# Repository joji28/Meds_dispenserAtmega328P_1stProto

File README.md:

# Meds_dispenserAtmega328P_1stProto
Smart Medicine Dispenser
Project Description
This automated medicine dispenser is designed to release medication at three scheduled times (morning, afternoon, and dinner) using stepper motors. The first prototype was built around an ATmega328P microcontroller (pulled from an Arduino UNO) and programmed using Atmel Studio 7.0 with an AVR 8051 USB ISP programmer.

Key Features
Time-Based Dispensing: Takes user input via Bluetooth (HC-05) to set the current time and three medication schedules.
Real-Time Tracking: Uses an RTC (DS3231) for accurate timekeeping.
Visual Feedback: Displays time and alerts on a 0.94" OLED screen.
Motor Control: Three 28BYJ-5V stepper motors (driven by ULN2003) rotate 45° to dispense pills when scheduled.
Power Management: A 12V input is stepped down to 5V using an AMS1117 regulator for safe operation.

How It Works
User Input Setup
The user sets the current time and three medication times via Bluetooth (HC-05).
The RTC (DS3231) is updated, and the schedule is displayed on the OLED for verification.

Automated Dispensing
The system continuously checks the RTC.
When the current time matches a scheduled time, the corresponding stepper motor rotates 45°, dispensing the medicine.
A confirmation message (e.g., "Afternoon medicine dispensed") appears on the OLED.

Daily Reset
The system loops indefinitely, dispensing medication at the same times every day.

Hardware Components
ATmega328P (from Arduino UNO) -> Main microcontroller (11.0592 MHz oscillator)
HC-05 Bluetooth Module ->	Wireless input for time settings
DS3231 RTC	-> Keeps accurate time for scheduling
0.94" OLED Display	-> Shows time, settings, and dispensing alerts
28BYJ-5V Stepper Motors (x3)	-> Rotate to dispense pills
ULN2003 Motor Drivers (x3)	-> Control stepper motors
AMS1117 5V Regulator ->	Converts 12V input to 5V for components
Rocker Switch ->	Power control

-I've also attached the schematics and pcbs(2 layers) design in kicad along with a video of testing components pls feel free to refer those.

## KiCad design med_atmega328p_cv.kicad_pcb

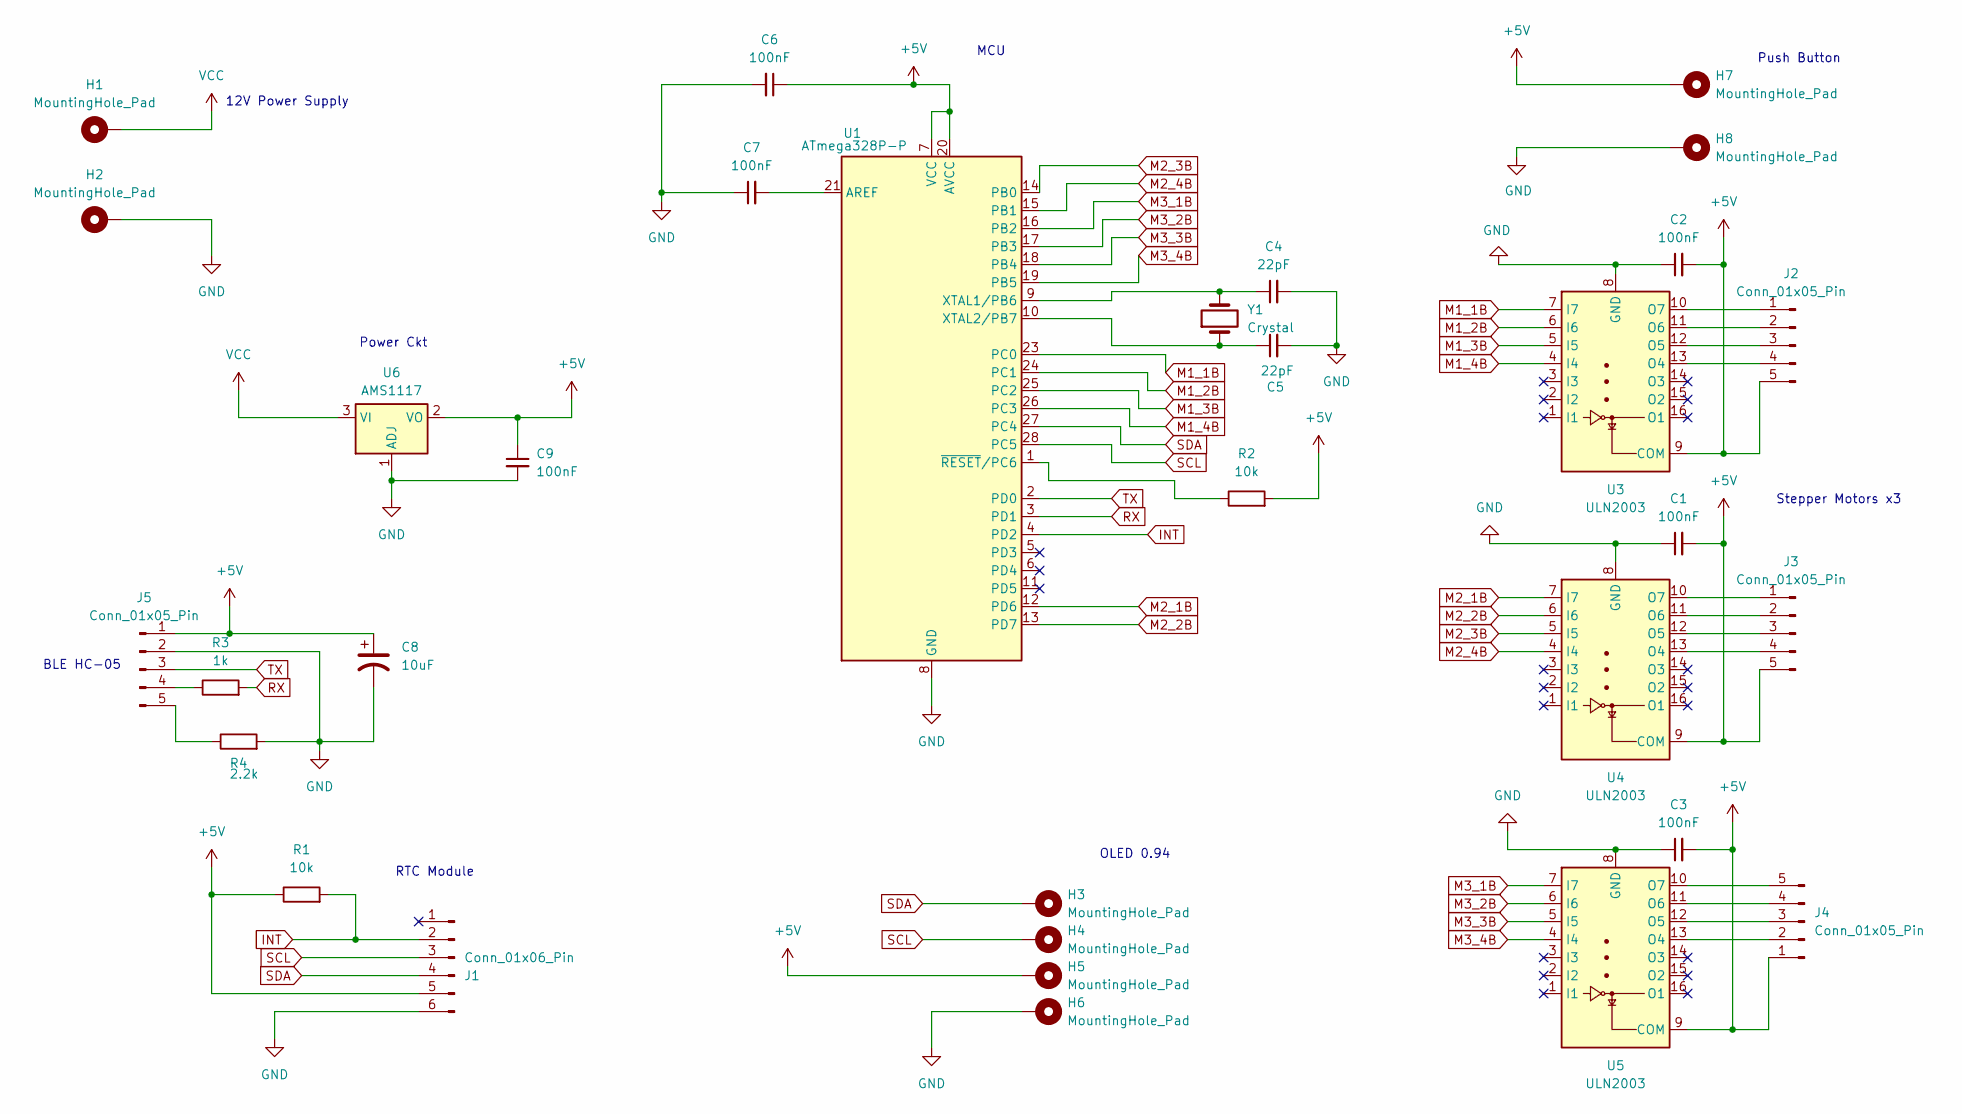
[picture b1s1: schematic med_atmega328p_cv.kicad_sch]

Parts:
C1, C2, C3, C6, C7, C9: 100nF; C_Disc_D3.0mm_W1.6mm_P2.50mm
C4, C5: 22pF; C_Disc_D3.0mm_W1.6mm_P2.50mm
C8: 10uF; CP_Radial_D6.3mm_P2.50mm
H1, H2, H3, H4, H5, H6, H7, H8: MountingHole_Pad; TestPoint_Pad_D4.0mm
J1: Conn_01x06_Pin; PinHeader_1x06_P2.54mm_Horizontal
J2, J3, J4, J5: Conn_01x05_Pin; PinHeader_1x05_P2.54mm_Horizontal
R1, R2: 10k; R_Axial_DIN0204_L3.6mm_D1.6mm_P5.08mm_Horizontal
R3: 1k; R_Axial_DIN0204_L3.6mm_D1.6mm_P5.08mm_Horizontal
R4: 2.2k; R_Axial_DIN0204_L3.6mm_D1.6mm_P5.08mm_Horizontal
U1: ATmega328P-P; DIP-28_W7.62mm
U3, U4, U5: ULN2003; CERDIP-16_W7.62mm_SideBrazed
U6: AMS1117; SOT-223-3_TabPin2
Y1: Crystal; Crystal_HC52-6mm_Vertical

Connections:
+5V: C1.2, C2.2, C3.2, C6.1, C8.1, C9.1, H5.1, H7.1, J1.5, J2.5, J3.5, J4.1, J5.1, R1.1, R2.2, U1.7 (VCC), U1.20 (AVCC), U3.9 (COM), U4.9 (COM), U5.9 (COM), U6.2 (VO)
GND: C1.1, C2.1, C3.1, C4.2, C5.2, C6.2, C7.1, C8.2, C9.2, H2.1, H6.1, H8.1, J1.6, J5.2, R4.2, U1.8 (GND), U1.22 (GND), U3.8 (GND), U4.8 (GND), U5.8 (GND), U6.1 (ADJ)
INT: J1.2, R1.2, U1.4 (PD2)
M1_1B: U1.23 (PC0), U3.7 (I7)
M1_2B: U1.24 (PC1), U3.6 (I6)
M1_3B: U1.25 (PC2), U3.5 (I5)
M1_4B: U1.26 (PC3), U3.4 (I4)
M2_1B: U1.12 (PD6), U4.7 (I7)
M2_2B: U1.13 (PD7), U4.6 (I6)
M2_3B: U1.14 (PB0), U4.5 (I5)
M2_4B: U1.15 (PB1), U4.4 (I4)
M3_1B: U1.16 (PB2), U5.7 (I7)
M3_2B: U1.17 (PB3), U5.6 (I6)
M3_3B: U1.18 (PB4), U5.5 (I5)
M3_4B: U1.19 (PB5), U5.4 (I4)
unnamed: J2.1, U3.10 (O7)
unnamed: J2.2, U3.11 (O6)
unnamed: J2.3, U3.12 (O5)
unnamed: J2.4, U3.13 (O4)
unnamed: J3.1, U4.10 (O7)
unnamed: J3.2, U4.11 (O6)
unnamed: J3.3, U4.12 (O5)
unnamed: J3.4, U4.13 (O4)
unnamed: J4.2, U5.13 (O4)
unnamed: J4.3, U5.12 (O5)
unnamed: J4.4, U5.11 (O6)
unnamed: J4.5, U5.10 (O7)
unnamed: J5.4, R3.1
unnamed: J5.5, R4.1
unnamed: C7.2, U1.21 (AREF)
unnamed: C4.1, U1.9 (XTAL1/PB6), Y1.2
unnamed: C5.1, U1.10 (XTAL2/PB7), Y1.1
unnamed: R2.1, U1.1 (~RESET/PC6)
RX: R3.2, U1.3 (PD1)
SCL: H4.1, J1.3, U1.28 (PC5)
SDA: H3.1, J1.4, U1.27 (PC4)
TX: J5.3, U1.2 (PD0)
VCC: H1.1, U6.3 (VI)

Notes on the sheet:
Push Button
12V Power Supply
RTC Module
MCU
Power Ckt
OLED 0.94
Stepper Motors x3
BLE HC-05

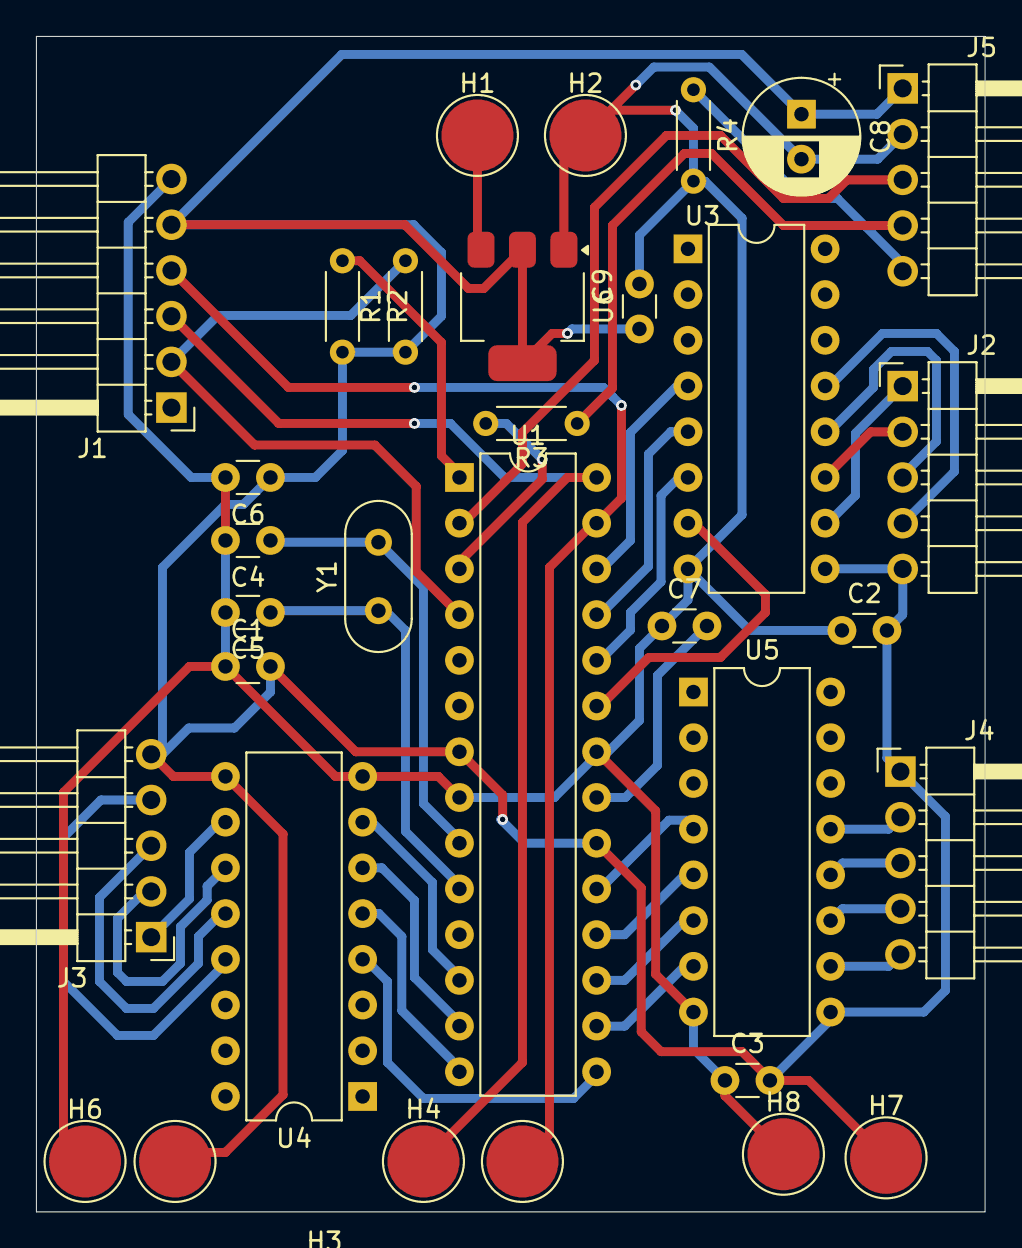
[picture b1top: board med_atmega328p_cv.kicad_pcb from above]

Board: 2 copper layers, 52.7 x 65.3 mm, 32 parts (0 on the bottom side), 38 nets.

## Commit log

2025-07-29 Add files via upload
    font.h was the library that helped me print ascii values like alphabets and numbers on my oled display cuz you need to enter ascii values of each alphabets for the atmega 8bit to process it and displ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
2025-07-29 Add files via upload
    a small testing video where the stepper moves 45 degrees when current time reaches the target time
